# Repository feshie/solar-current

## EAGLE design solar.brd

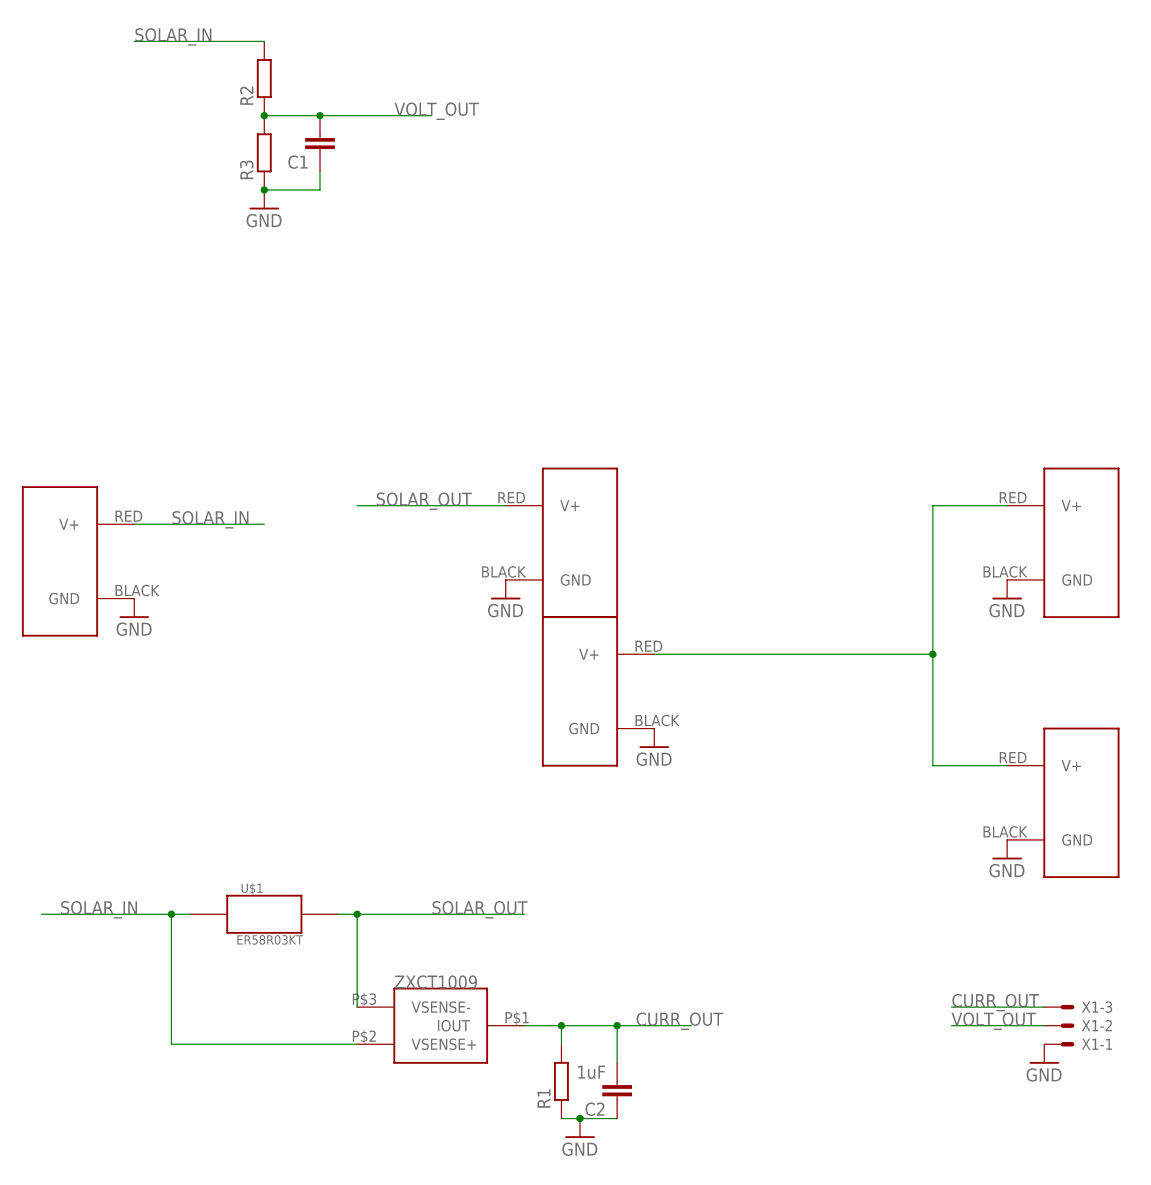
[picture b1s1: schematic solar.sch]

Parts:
C1: C-EUC0805; C0805
C2: 1uF; C0805
J1, J2, J3, J4, J5: POWERPOLE_POWER25A; POWERPOLE_PAIR_25A
R1, R2, R3: R-EU_R0805; R0805
U$1: ER58R03KT
U$2: ZXCT1009; ZXCT1009-SOT
X1: KK-156-3

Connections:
CURR_OUT: C2.2, R1.2, U$2.P$1 (IOUT), X1.3
GND: C1.1, C2.1, J1.BLACK (GND), J2.BLACK (GND), J3.BLACK (GND), J4.BLACK (GND), J5.BLACK (GND), R1.1, R3.1, X1.1
unnamed: J2.RED (V+), J4.RED (V+), J5.RED (V+)
SOLAR_IN: J1.RED (V+), R2.2, U$1.P$1, U$2.P$2 (VSENSE+)
SOLAR_OUT: J3.RED (V+), U$1.P$2, U$2.P$3 (VSENSE-)
VOLT_OUT: C1.2, R2.1, R3.2, X1.2

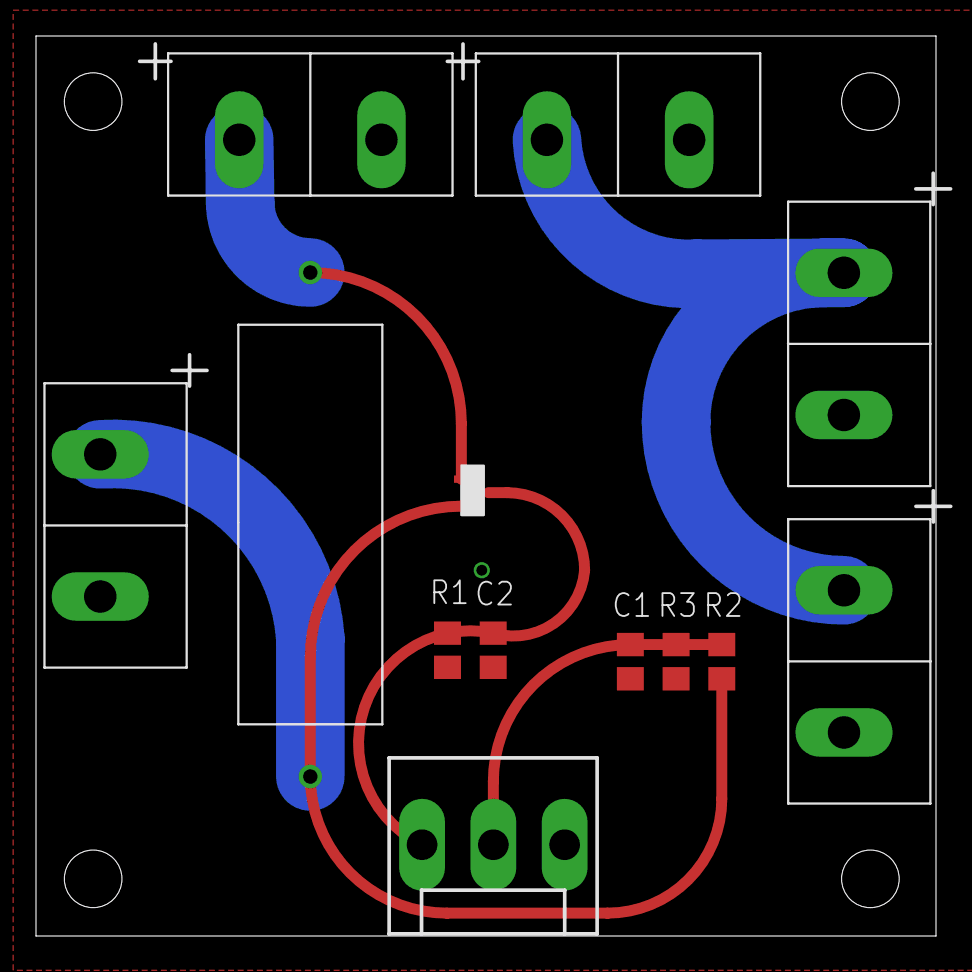
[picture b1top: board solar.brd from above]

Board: 2 copper layers, 50.0 x 50.0 mm, 13 parts (0 on the bottom side), 6 nets.

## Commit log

2014-05-02 first version of solar current measuring board
2014-05-02 Uses PCB mount instead of cable for power pole
2014-05-12 now uses smaller frame
